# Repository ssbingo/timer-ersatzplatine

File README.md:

#  Feeder-Relais

<p align="center">
  
</p>

> **Herkunft:** Dieses Projekt ist der Umbau eines **SuperFish / Koi-Pro Fish Feeder** (Futterautomat von Aquadistri — [Produktreihe](https://aquadistri.com/de/brands/koi-pro/einrichtung-zubehoer/zubehoer/) · [Original-Handbuch (PDF)](docs/Koi-Pro-FishFeeder-Original-Manual.pdf)) — die defekte originale Zeitschaltplatine wird ersetzt. **Gehäuse-Rückteil und Platine orientieren sich an den Maßen der Originalsteuerung**, damit beides exakt in das vorhandene Gehäuse passt.

**230-V-Timer-Steuerung zum Selbstbau — ESP32-C3 · OLED · PhotoMOS · externer Shelly 1PM Mini Gen4**

Das Feeder-Relais ist eine selbstgebaute Steuerplatine, die eine 230-Volt-Last
auf Knopfdruck für eine **einstellbare Zeit** einschaltet und danach von allein
wieder abschaltet. Der Name stammt aus dem ursprünglichen Einsatz: Sie ersetzt
die defekte Zeitschaltplatine eines **Futterautomaten** (englisch *feeder*).
Weil sie im Kern nur „einen Schalter für eine gewisse Zeit drückt“, eignet sie
sich für jede Last, die zeitgesteuert geschaltet werden soll — Pumpe,
Futtermotor, Lüfter, Licht.

Drei Taster lösen drei getrennt einstellbare Zeiten aus (Standard 5/10/15 s),
ein OLED zeigt WLAN, Uhrzeit und den Countdown, und eine für Handys optimierte
Weboberfläche erlaubt Bedienung und Konfiguration im Heimnetz — **ohne App und
ohne Cloud**. Das eigentliche Schalten und die Leistungsmessung übernimmt ein
**externer Shelly 1PM Mini Gen4**; die Platine steuert dessen SW-Eingang über ein
**PhotoMOS-Relais galvanisch getrennt** an. Dadurch ist die Kernfunktion
**WLAN-unabhängig**.

> ### ⚠️ 230 Volt — Lebensgefahr
> Netzspannung kann tödlich sein. Aufbau, Prüfung und Inbetriebnahme der
> 230-V-Seite gehören in die Hände einer **Elektrofachkraft** oder unterwiesenen
> Person. Alle Tests, die ohne Fachkraft möglich sind, laufen **ausschließlich
> über USB und ohne jede Netzspannung**. Bitte zuerst Kapitel 2 des Handbuchs
> lesen.

---

## 🌍 Sprachen · Languages

| Sprache | README | Handbuch (PDF) | 🌐 Online |
|--------|--------|----------------|--------|
| 🇩🇪 **Deutsch** (Original) | [README.md](README.md) | [docs/handbuch/Feeder-Relais-Handbuch.pdf](docs/handbuch/Feeder-Relais-Handbuch.pdf) | [Online](https://ssbingo.github.io/timer-ersatzplatine/) |
| 🇬🇧 English | [docs/en/README.md](docs/en/README.md) | [docs/en/Feeder-Relais-Manual.pdf](docs/en/Feeder-Relais-Manual.pdf) | [Online](https://ssbingo.github.io/timer-ersatzplatine/en.html) |
| 🇫🇷 Français | [docs/fr/README.md](docs/fr/README.md) | [docs/fr/Feeder-Relais-Manuel.pdf](docs/fr/Feeder-Relais-Manuel.pdf) | [Online](https://ssbingo.github.io/timer-ersatzplatine/fr.html) |
| 🇳🇱 Nederlands | [docs/nl/README.md](docs/nl/README.md) | [docs/nl/Feeder-Relais-Handleiding.pdf](docs/nl/Feeder-Relais-Handleiding.pdf) | [Online](https://ssbingo.github.io/timer-ersatzplatine/nl.html) |
| 🇪🇸 Español | [docs/es/README.md](docs/es/README.md) | [docs/es/Feeder-Relais-Manual.pdf](docs/es/Feeder-Relais-Manual.pdf) | [Online](https://ssbingo.github.io/timer-ersatzplatine/es.html) |
| 🇮🇹 Italiano | [docs/it/README.md](docs/it/README.md) | [docs/it/Feeder-Relais-Manuale.pdf](docs/it/Feeder-Relais-Manuale.pdf) | [Online](https://ssbingo.github.io/timer-ersatzplatine/it.html) |

---

## Inhalt

1. [Überblick](#überblick)
2. [Die Signalkette](#die-signalkette)
3. [Die Platine (Hardware v3)](#die-platine-hardware-v3)
4. [Die Firmware](#die-firmware)
5. [Bedienung](#bedienung)
6. [Das Gehäuse (3D-Druck)](#das-gehäuse-3d-druck)
7. [Anbindung an ioBroker](#anbindung-an-iobroker)
8. [Nachbau & Handbuch](#nachbau--handbuch)
9. [Projektstruktur](#projektstruktur)
10. [Status](#status)
11. [Lizenz](#lizenz)

---

## Überblick

Das Gerät ersetzt eine originale Timer-Platine hinter einer vorhandenen
Frontplatte. Es besteht aus vier gut trennbaren Bausteinen:

- **Platine** (`kicad-v3/`) — ESP32-C3, Netzteil, PhotoMOS und die 230-V-Klemmen,
  vierlagig, gesamte Elektronik auf der Rückseite.
- **Firmware** (`firmware/`) — ESPHome-Projekt mit eigener Mobil-Web-App,
  JSON-Schnittstelle, NTP-Uhr, OLED-Anzeige, Status-LED und mehrsprachiger
  Bedienung.
- **Gehäuse** (`box/`) — 3D-gedrucktes Rückteil (35 mm tief), das Platine *und*
  den externen Shelly aufnimmt; das Vorderteil ist die vorhandene Frontplatte.
- **Externer Shelly 1PM Mini Gen4** — das zertifizierte Schaltrelais mit
  Leistungsmessung, außerhalb der Platine verdrahtet.

Die **Aufgabenteilung** ist der Kern des Konzepts: Der ESP misst die Zeit und
gibt ein galvanisch getrenntes Hardware-Signal an den Shelly; der Shelly schaltet
die Last und misst die Leistung. Fällt das WLAN aus, laufen Tasten, Timer und
Schalten trotzdem weiter — nur die Fernbedienung ruht.

## Die Signalkette

Vom Tastendruck bis zur geschalteten Last durchläuft das Signal fünf Stationen,
jede mit genau einer Aufgabe:

```
Taste  ─►  ESP32-C3  ─►  330 Ω  ─►  PhotoMOS  ─►  Shelly 1PM  ─►  Last
S1–S3      zählt die     begrenzt    schaltet      schaltet und     (Pumpe,
           Zeit, malt    den LED-    galvanisch     misst die        Futter-
           das OLED      Strom       getrennt       230-V-Last       motor …)
```

Der ESP arbeitet mit ungefährlichen 3,3 V und darf 230 V niemals direkt berühren.
Der **PhotoMOS** ist die Brücke: Er trennt Klein- und Netzspannung vollständig
durch *Licht*. Der Shelly wird auf **Switch/Follow** gestellt — sein Relais ist
genau so lange an, wie unser Signal anliegt; das gesamte Timing bleibt beim ESP.

## Die Platine (Hardware v3)

Die aktuelle Version 3 liegt fertig als KiCad-Projekt unter `kicad-v3/`.

- **Außenmaß** 101,6 × 77,5 mm, **vierlagig** (1,6 mm).
- **Gesamte Elektronik auf der Rückseite** — vorne bleiben nur die drei Taster
  und die OLED-Buchse (alles, was bedient oder gesehen wird).
- Die beiden **Innenlagen sind durchgehende Masseflächen** im
  Kleinspannungsbereich → störungsarm, stabiles WLAN.
- **Netzspannung nur außen:** Die fünf 230-V-Netze liegen ausschließlich auf den
  Außenlagen, unten links, in einer eigenen Netzklasse mit breiteren Bahnen.
- **6-mm-Kriechstrecke** zwischen jedem 230-V-Netz und jeder Kleinspannung — als
  feste KiCad-Prüfregel (`.kicad_dru`) hinterlegt. Einzige Ausnahme ist das
  PhotoMOS K1: Sein Gehäuse *ist* die zertifizierte Trennstelle.

### GPIO-Belegung — verbindlicher Abgleich Platine ↔ Firmware

Diese Zuordnung muss auf beiden Seiten exakt übereinstimmen, sonst funktioniert
das Gerät nicht:

| ESP-Pin | Firmware | Platine / Netz | Funktion |
|---------|----------|----------------|----------|
| **GPIO3** | `btn_s1` (Eingang, Pull-up, invertiert) | Pad 3 → `/BTN1` | Taster **S1 Down/Manual** (T1) → Timer 1 |
| **GPIO4** | `btn_s2` | Pad 4 → `/BTN2` | Taster **S2 SET** (T2) → Timer 2 / lang: Menü |
| **GPIO5** | `btn_s3` | Pad 5 → `/BTN3` | Taster **S3 UP** (T3) → Timer 3 / lang: Stop |
| **GPIO6** | `shelly_trigger` (Ausgang) | Pad 6 → `/PMOS_DRV` → R1 330 Ω → K1-LED | PhotoMOS-Treiber: HIGH = Last ein |
| **GPIO7** | `i2c: sda` (400 kHz) | Pad 7 → `/SDA` → OLED J2.4 | I²C-Datenleitung zum OLED |
| **GPIO8** | `status_led` (WS2812, GRB) | modulintern (Pad 8 frei) | Onboard-RGB-Status-LED (Ampel) |
| **GPIO9** | `i2c: scl` (400 kHz) | Pad 9 → `/SCL` → OLED J2.3 | I²C-Taktleitung zum OLED (Adresse 0x3C) |
| **5V / GND** | Modulversorgung | `/+5V` / `GND` vom Netzteil | Versorgung + gemeinsame Masse |
| **3V3** | Onboard-Regler | `/+3V3` → OLED-VCC | 3,3 V für das OLED |

> **Wichtig:** SDA liegt bewusst auf **GPIO7**, nicht GPIO8 — auf GPIO8 sitzt die
> Onboard-WS2812. Läge dort I²C, bliebe das OLED schwarz und der Datenverkehr
> würde die LED stören.

### Anschlussklemmen und Netze

| Klemme | Anschluss | Belegung |
|--------|-----------|------------------|
| **X1** | Netzeingang | 1 = N, 2 = L_IN (230 V herein) |
| **X2** | Lastabgang | 1 = O (geschaltet), 2 = N |
| **X3** | Snubber | 1 = O, 2 = N — optionales RC-Glied für induktive Lasten |
| **J1** | Shelly (extern) | 1 = SW, 2 = O, 3 = L, 4 = N |
| **J2** | OLED | GND / VCC / SCL / SDA (aufgesteckt) |

Die fünf 230-V-Netze der Netzklasse „230V“: `L_IN` (ungesichert, X1→F1),
`L_F` (abgesichert, F1→RV1/PS1/K1.3/Shelly-L), `N` (Neutral), `SW_SHELLY`
(geschaltet, K1.4→Shelly-SW) und `O_LAST` (geschaltet, Shelly-O→X2/X3).

### Wichtige Bauteile

| Kennung | Bauteil | Funktion |
|---------|---------|------------------|
| **U1** | ESP32-C3 Super Mini | Mikrocontroller mit WLAN, 5 V→3,3 V; trägt die WS2812 auf GPIO8 |
| **K1** | PhotoMOS G3VM-601AY2 (o. -601BY / AQY216) | Galvanische Trennung 3,3 V ↔ 230 V, **≥ 400 V** |
| **PS1** | AC/DC-Modul TSP-05 (5 V / 3 W) | Netzteil aus L_F + N |
| **R1** | 330 Ω | Vorwiderstand der K1-LED (~6 mA) |
| **C1 / C2** | 220 µF / 100 nF | 5-V-Puffer (WLAN-Spitzen) + Abblockung |
| **F1** | 1 A träge, 5×20 mm | primärseitige Feinsicherung (X1→F1→L_F) |
| **RV1** | Varistor S14K275 | Überspannungsschutz zwischen L_F und N |
| **SW1–3** | Taster 6×6 mm | die drei Kurzhubtaster (Position fix, Frontplatte) |

## Die Firmware

Die Firmware ist ein **ESPHome**-Projekt (`firmware/timer-relais-c3.yaml`) mit
eigenen C++-Erweiterungen. Gerätename/Hostname: **`feeder-relais`**
(→ `http://feeder-relais.local`).

- **Timer-Logik:** drei unabhängige Zeiten (1–600 s), im laufenden Betrieb per
  Web änderbar; kurzer Tastendruck startet, langer Druck auf UP stoppt alles.
- **Eigene Mobil-Web-App + JSON-API** (`firmware/timer_web.h`) auf Port 80 —
  kein Cloud-Dienst. Endpunkte: `/api/status`, `/api/trigger`, `/api/stop`,
  `/api/config`, `/api/net`, `/api/wifi`, `/api/reboot`.
- **OLED-Anzeige** (SSD1306 128×32): WLAN-Empfang, große NTP-Uhr, Datum, freier
  Speicher; im Timerlauf der Sekunden-Countdown. Anzeige um 180° gedreht (an die
  Einbaulage angepasst).
- **Status-Ampel** über die Onboard-WS2812 (GPIO8): **grün** = bereit,
  **gelb** = Timer läuft, **rot** = Störung.
- **Netzwerk-Konfiguration zur Laufzeit** (`firmware/net_config.h`): IP-Modus
  DHCP/statisch, NTP-Server, Hostname, 802.11k/v-Roaming.
- **Mehrsprachig** (Web + OLED): Deutsch / Englisch / Französisch, geräteweit
  umschaltbar.
- **Provisioning per Captive-Portal** — kein WLAN-Passwort einkompiliert; die
  Zugangsdaten überstehen ein Update.
- **Drahtlose Updates (OTA)** über `web_server`-Plattform (`POST /update`) sowie
  ein Log-/Debug-Ringpuffer (`/api/log`).

Fertige Flash-Images (factory + OTA) liegen unter `firmware/build/`.

## Bedienung

**Am Gerät** — drei Taster:

| Taste | kurz | lang |
|-------|------|--------------|
| **S1** Down/Manual | Timer 1 auslösen | — |
| **S2** SET | Timer 2 auslösen | ≥ 3 s: Info-Menü (mit S1/S3 blättern) |
| **S3** UP | Timer 3 auslösen | ≥ 1,2 s: alle Timer stoppen |

**Mobil** — im Browser `http://feeder-relais.local`: Timer auslösen, die drei
Zeiten einstellen, Netzwerk- und Statuswerte einsehen, Sprache wählen.

## Das Gehäuse (3D-Druck)

Das Gehäuse besteht aus dem vorhandenen **Vorderteil** (Originalfrontplatte mit
Sichtfenster und Tast-Stößeln) und einem selbst gedruckten **Rückteil**:

- **Produktionsgehäuse:** `box/feeder_back_Shelly_35mm.stl` — das zu druckende
  Rückteil **mit integrierten Halterungen für den Shelly und den Snubber**.
- Basis-/Parametervariante: `box/feeder_back.scad` (OpenSCAD) → `box/feeder_back_35mm.stl`
  (ohne Shelly-/Snubber-Halter), zum Anpassen der Maße.
- **35 mm tief** (statt originaler 5,7 mm), damit Platine *und* Shelly hineinpassen;
  Außenmaß 109,8 × 90,8 mm.
- Wandaufbau: Dichtkante oben **1,3 mm**, verstärkte Außenwand darunter **2,5 mm**,
  Boden **2,5 mm**. Sechs Schraubdome (Raster 45 × 70 mm) mit tiefem Senkkanal für
  die kurzen Originalschrauben; Aufhängelasche mit Schlüsselloch.
- `box/Timer-Ersatzplatine-v3-BOARD.stl` ist eine **1:1-Attrappe** der Platine —
  flach drucken und einlegen, um die Passung zu prüfen, **bevor** die echte
  Platine bestellt wird.

## Anbindung an ioBroker

Das Feeder-Relais ist die **Hardware-Seite** eines Futterautomaten und lässt sich
gut in eine Hausautomatisierung einbinden:

- Der **externe Shelly 1PM Mini Gen4** wird in ioBroker über den
  **Shelly-Adapter** nativ eingebunden — Schaltzustand und Leistungsmessung sind
  dort direkt sichtbar und steuerbar.
- Die **eigene JSON-API** des Geräts (`/api/status | trigger | stop | config`)
  lässt sich per REST/Skript (z. B. `simple-api`, JavaScript-Adapter) auslesen
  und bedienen — für Timer-Auslösung und Statusabfrage. Ein Timer-Start lässt sich
  mit `&src=adapter` kennzeichnen; die Quelle des letzten Starts steht dann im
  Status-Feld `trg` (`button`/`api`/`adapter`) und in einer Log-Zeile der Platine.

Im selben „Smart-Pond/Feeder“-Umfeld gibt es zwei passende Adapter desselben
Autors, die die **Software-Seite** bilden:

- **[ioBroker.automatic-feeder](https://github.com/ssbingo/ioBroker.automatic-feeder)**
  — Zeitplanung, Temperaturmodell, Sonnenauf-/-untergang, Pausen und
  Benachrichtigungen für einen Fisch-/Koi-/Teichfutterautomaten.
- **[ioBroker.vis-2-widgets-automatic-feeder](https://github.com/ssbingo/ioBroker.vis-2-widgets-automatic-feeder)**
  — fertige vis-2-Dashboard-Widgets (Live-Ansicht und Fernbedienung) für den
  Adapter oben.

So bildet die Hardware (dieses Gerät + Shelly) zusammen mit den beiden Adaptern
eine durchgängige Kette von der Taste bis zum Dashboard.

## Nachbau & Handbuch

Ein **vollständiges, anfängertaugliches Handbuch** führt Schritt für Schritt vom
leeren Board bis zum fertigen Gerät — mit Sicherheit, Einkaufsliste,
Platinenfertigung, Bestückung, Firmware-Flashen und Inbetriebnahme, inklusive
klickbarem Inhaltsverzeichnis:

**➡️ [docs/handbuch/Feeder-Relais-Handbuch.pdf](docs/handbuch/Feeder-Relais-Handbuch.pdf)**
(Übersetzungen siehe [Sprachen-Tabelle](#-sprachen--languages) oben.)

Firmware flashen (ESP per USB-C):

```bash
esphome run firmware/timer-relais-c3.yaml
```

## Projektstruktur

```
kicad-v3/     Platine v3 (KiCad: Schaltplan, Layout, 6-mm-Regel, Footprints, 3D-Modelle)
box/          Gehäuse-Rückteil (OpenSCAD-Quelle + STL) und Platinen-Attrappe
firmware/     ESPHome-Firmware (.yaml + .h), fertige Flash-Images in build/
docs/         Handbuch-PDF (deutsch) und Übersetzungen unter docs/<sprache>/
README.md     dieses Dokument (deutsch; Übersetzungen unter docs/<sprache>/)
```

## Status

**Version 3 fertig entwickelt — vor der Fertigung.** Platine 4-lagig geroutet
(DRC ohne echte Fehler), Board ↔ Firmware abgeglichen (OLED-SDA auf GPIO7),
Gehäuse und Dokumentation fertig. Offen: Gerber frisch erzeugen, Passprobe der
Attrappe, 4-Lagen-Bestellung, Aufbau und Funktionstest.

## Lizenz

Dieses Projekt (Hardware, Firmware, Gehäuse und Dokumentation) steht unter der
Lizenz **Creative Commons Namensnennung – Nicht kommerziell – Weitergabe unter
gleichen Bedingungen 4.0 International (CC BY-NC-SA 4.0)**.

© 2026 Silvio Sternitzke

Es steht dir frei:

- **Teilen** — das Material vervielfältigen und weiterverbreiten,
- **Bearbeiten** — es umgestalten und darauf aufbauen,

unter den folgenden Bedingungen:

- **Namensnennung (BY)** — nenne den Urheber, verlinke die Lizenz und gib an, ob
  Änderungen vorgenommen wurden.
- **Nicht kommerziell (NC)** — nicht für kommerzielle Zwecke.
- **Weitergabe unter gleichen Bedingungen (SA)** — Bearbeitungen müssen unter
  derselben Lizenz weitergegeben werden.
- **Keine weiteren Einschränkungen** — keine zusätzlichen Klauseln oder
  technischen Maßnahmen, die anderen etwas rechtlich Erlaubtes verwehren.

Lizenztext: <https://creativecommons.org/licenses/by-nc-sa/4.0/deed.de> ·
vollständiger Rechtstext siehe [LICENSE](LICENSE).

> **Haftungsausschluss:** Der Nachbau erfolgt auf eigene Verantwortung.
> 230 Volt sind lebensgefährlich. Das Material wird ohne Gewähr bereitgestellt;
> jede Haftung für Schäden ist ausgeschlossen. Im Zweifel eine Elektrofachkraft
> hinzuziehen.

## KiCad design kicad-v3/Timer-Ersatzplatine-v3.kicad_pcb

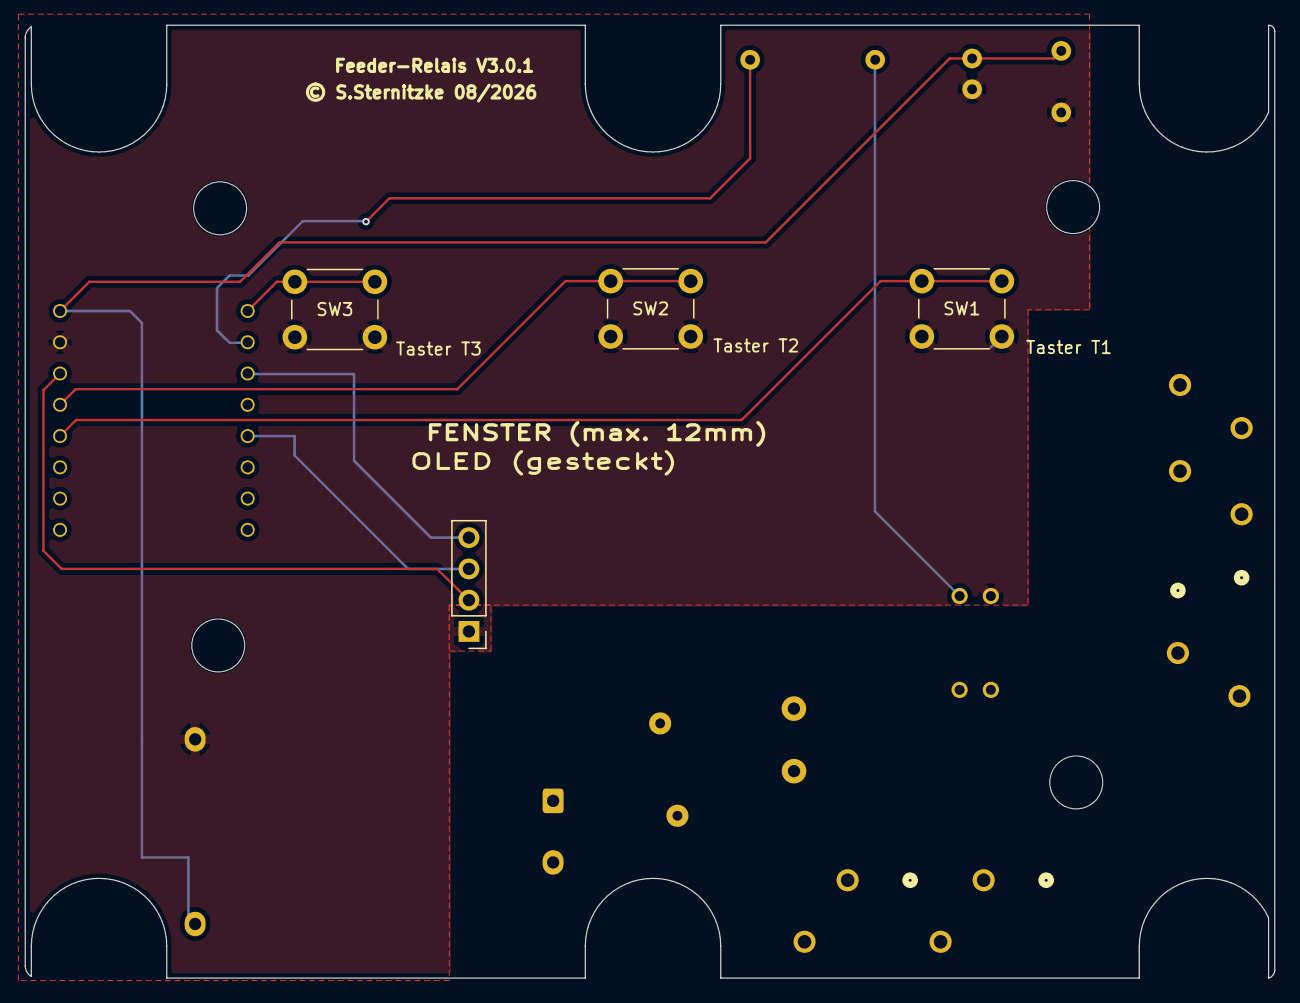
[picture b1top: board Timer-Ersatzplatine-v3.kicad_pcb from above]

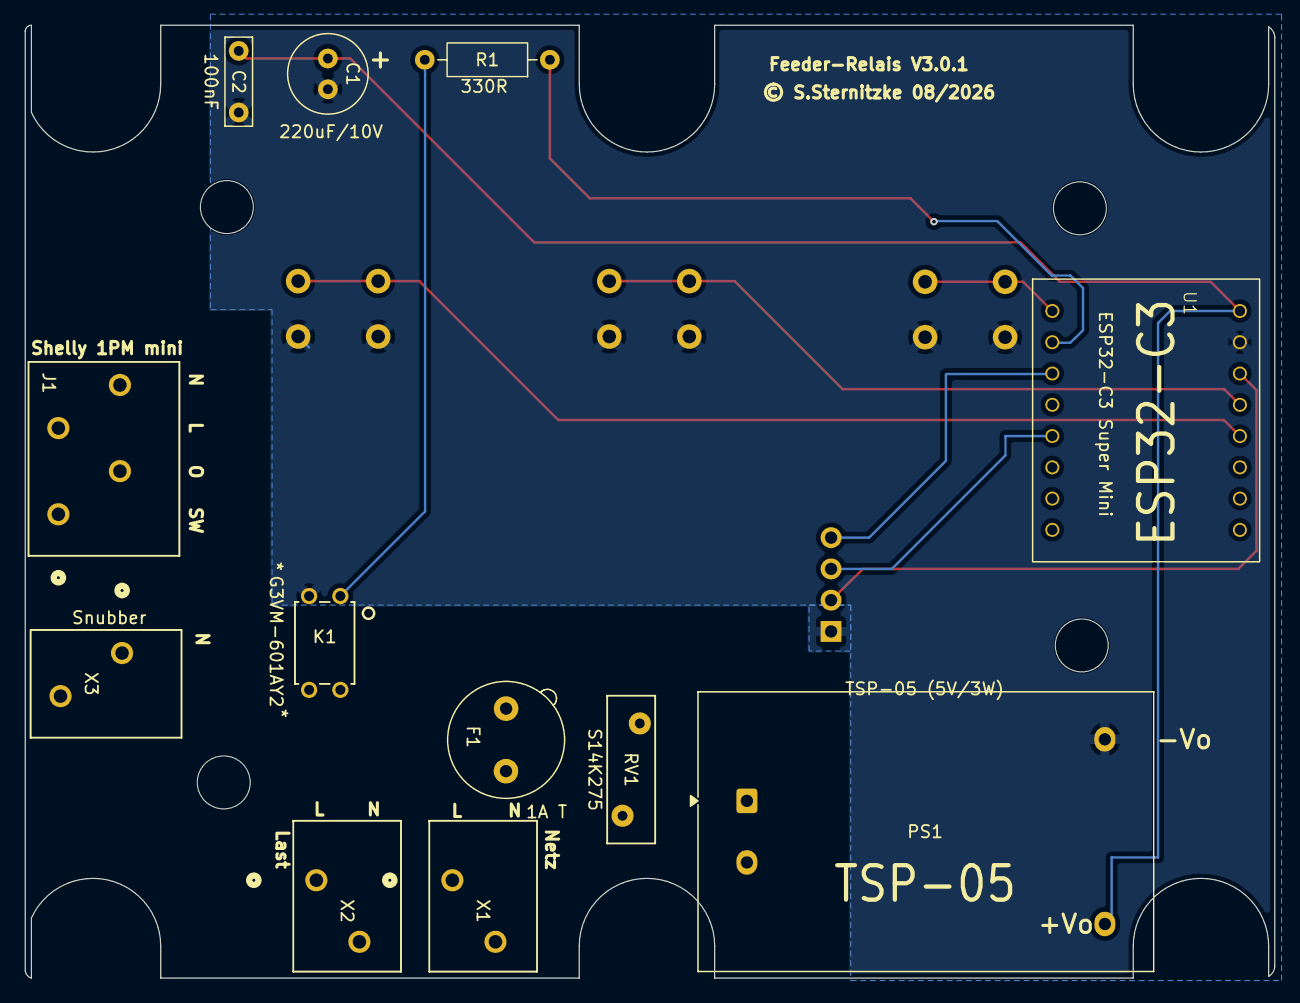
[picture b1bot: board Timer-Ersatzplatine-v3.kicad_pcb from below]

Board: 4 copper layers, 101.5 x 77.4 mm, 20 parts (12 on the bottom side), 15 nets.

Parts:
C1: 220uF/10V; C_Radial_D6.3mm_H11.0mm_P2.50mm
C2: 100nF; C_Rect_L7.0mm_W2.0mm_P5.00mm
F1: 1A T; Fuseholder_TR5_Littelfuse_No560_No460
J1: 250-204; CONN4_250-204_WAG
J4: OLED SSD1306 0,91 Zoll; PinHeader_1x04_P2.54mm_Vertical
K1: G3VM-601AY2; A-DIP4_THD_OMR
PS1: TSP-05 (5V/3W); Converter_ACDC_Hi-Link_HLK-PMxx
R1: 330R; R_Axial_DIN0207_L6.3mm_D2.5mm_P10.16mm_Horizontal
REF1, REF2, REF3, REF4: MountingHole_4.3mm_M4
RV1: S14K275; RV_Disc_D12mm_W3.9mm_P7.5mm
SW1: Taster T1; SW_PUSH_6mm
SW2: Taster T2; SW_PUSH_6mm
SW3: Taster T3; SW_PUSH_6mm
U1: ESP32-C3 Super Mini; ESP32-C3-SuperMini
X1: Netz; CONN2_250-202_WAG
X2: Last; CONN2_250-202_WAG
X3: Snubber; CONN2_250-202_WAG

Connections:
/+3V3: J4.2, U1.3V3
/+5V: C1.1, C2.1, PS1.4 (GND), U1.5V
/BTN1: SW1.1, U1.3 (GPIO3)
/BTN2: SW2.1, U1.4 (GPIO4)
/BTN3: SW3.1, U1.5 (GPIO5)
/L_F: F1.2, J1.3, K1.3, PS1.1 (AC-L), RV1.2
/L_IN: F1.1, X1.1
/N: J1.4, PS1.2 (AC-N), RV1.1, X1.2, X2.2, X3.1
/O_LAST: J1.2, X2.1, X3.2
/PMOS_DRV: R1.1, U1.6 (GPIO6)
/SCL: J4.3, U1.9 (GPIO9/SCL)
/SDA: J4.4, U1.7 (GPIO7/SDA)
/SW_SHELLY: J1.1, K1.4
GND: C1.2, C2.2, J4.1, K1.2, PS1.3 (+5V), SW1.2, SW2.2, SW3.2, U1.G
unnamed: K1.1, R1.2

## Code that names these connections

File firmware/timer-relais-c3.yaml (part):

# =====================================================================
# Timer-Ersatzplatine: ESP32-C3 Super Mini + OLED 0,91" + PhotoMOS
# Pinbelegung passend zum KiCad-Schaltplan timer_ersatzplatine.kicad_sch
#   Taster S1/S2/S3 = Down/Manual / SET / UP: GPIO3 / GPIO4 / GPIO5
#     (gegen GND, interne Pullups)
#   PhotoMOS (-> Shelly SW): GPIO6 (ueber 330R an LED-Anode)
#   I2C OLED: SDA=GPIO7, SCL=GPIO9  (SDA war GPIO8 - kollidiert mit der RGB-LED!)
#   RGB-Status-LED (WS2812, onboard Super Mini): GPIO8
# =====================================================================

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
switch:
  - platform: gpio
    pin: GPIO6
    id: shelly_trigger
    name: "Shelly-Trigger"
    restore_mode: ALWAYS_OFF
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  # S1 = Down / Manual : kurz -> Timer 1 (im Menue: vorblaettern)
  - platform: gpio
    pin:
      number: GPIO3
      mode:
        input: true
        pullup: true
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  # S2 = SET : kurz -> Timer 2 (im Menue: schliessen) ; lang >=3 s -> Menue
  - platform: gpio
    pin:
      number: GPIO4
      mode:
        input: true
        pullup: true
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  # S3 = UP : kurz -> Timer 3 (im Menue: zurueckblaettern) ; lang >=1,2 s -> alles STOP
  - platform: gpio
    pin:
      number: GPIO5
      mode:
        input: true
        pullup: true
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      id: wifi_mac_txt

i2c:
  sda: GPIO7            # war GPIO8 -> dort sitzt die Onboard-RGB-LED (WS2812)
  scl: GPIO9
  frequency: 400kHz

# Onboard-RGB-LED (WS2812 auf GPIO8) als dezente Status-LED (gedimmt).
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

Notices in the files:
kicad-v3/Timer-Ersatzplatine-v3.kicad_pcb:
© S.Sternitzke
© S.Sternitzke 08/2026
